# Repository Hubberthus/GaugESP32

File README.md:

# GaugESP32
A merge of the [SparkFun ESP32 Thing](https://www.sparkfun.com/products/13907) and [SparkFun Battery Babysitter](https://www.sparkfun.com/products/13777) boards

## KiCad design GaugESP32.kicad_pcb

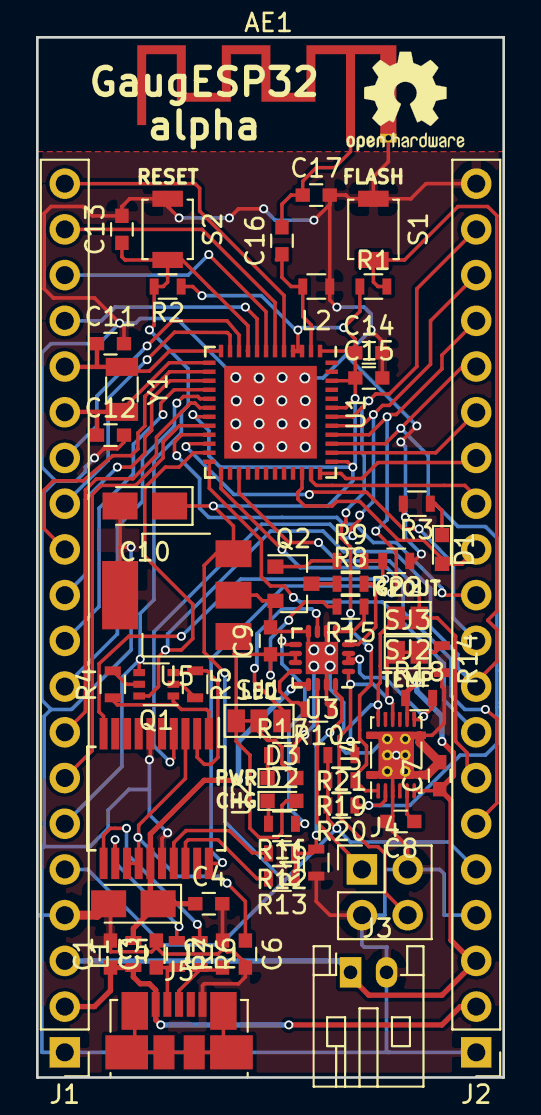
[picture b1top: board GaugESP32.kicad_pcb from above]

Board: 2 copper layers, 25.9 x 57.8 mm, 63 parts (0 on the bottom side), 64 nets.

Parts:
AE1: Antenna_Shield; Texas_SWRA117D_2.4GHz_Left
C1, C4, C6, C13, C15: 0.1uF; C_0603
C2, C3: 47pF; C_0603
C5, C10: 4.7F; CP_Tantalum_Case-A_EIA-3216-18_Reflow
C7, C9: 1uF; C_0603
C8: 0.47uF; C_0603
C11, C12: 15pF; C_0603
C14: 10uF; C_0603
C16: 4.7pF; C_0603
C17: 2.7pF; C_0603
D1: BLUE; LED_0603
D2: YELLOW; LED_0603
D3: RED; LED_0603
J1, J2: Conn_01x20; Pin_Header_Straight_1x20_Pitch2.54mm
J3: JST-PH; JST_PH_S2B-PH-K_02x2.00mm_Angled
J4: Conn_02x02_Counter_Clockwise; Pin_Header_Straight_2x02_Pitch2.54mm
J5: Micro USB-B; USB_Micro-B_Molex_47346-0001
L1: 600R/2A; L_0603
L2: 1.6nH; L_0603
Q1: MBT3946DW1T1; SOT-363_SC-70-6
Q2: BC847; SOT-23
R1, R2, R4, R5, R14, R15: 10k; R_0603
R3: 330; R_0603
R6, R7: 27; R_0603
R8: 100k; R_0603
R9: 470; R_0603
R10: 1.1k; R_0603
R11: 8.9k; R_0603
R12: 2.4k; R_0603
R13: 860; R_0603
R16: 180; R_0603
R17: 1k; R_0603
R18: 0.01; R_0603
R19, R20, R21: 4.7k; R_0603
R22: 2.2k; R_0603
S1: FLASH; SW_SPST_B3U-1000P
S2: RESET; SW_SPST_B3U-1000P
SJ1: GS3
SJ2, SJ3: GS2
U1: ESP32PICO_D4; ESP32_PICO_D4
U2: FT231XS; SSOP-20_5.3x7.2mm_Pitch0.65mm
U3: BQ24075; QFN-16-1EP_3x3mm_Pitch0.5mm
U4: BQ27441-G1; Texas_S-PDSO-N12
U5: LM3940; SOT-223
Y1: 32.768kHz; Crystal_SMD_3215-2pin_3.2x1.5mm

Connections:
+3.3VA: C10.1, C14.1, C15.1, J1.5, J2.5, R1.1, R2.1, R19.2, R20.2, R21.2, U1.1, U1.3, U1.4, U1.19, U1.37, U1.43, U1.46, U5.3
+5V: C4.1, C5.1, L1.2, U2.15, U3.13
+BATT: R18.2, U3.2, U3.3, U4.7
/1.8V: C8.1, U4.5
BCD#: R13.2, U2.18
DTR: Q1.1, R4.1, U2.1
EN: C13.1, J1.6, Q1.4, R2.2, S2.2, U1.9
GND: AE1.2, C1.2, C2.2, C3.2, C4.2, C5.2, C6.2, C7.2, C8.2, C9.2, C10.2, C11.2, C12.2, C13.2, C14.2, C15.2, C17.2, J1.1, J1.4, J2.1, J2.4, J2.20, J3.2, J4.2, J4.3, J5.5, L2.1, Q2.2, R3.2, R10.1, R11.1, R14.2, R17.2, R22.1, S1.1, S2.1, U1.49, U2.6, U2.16, U3.6, U3.8, U3.15, U3.17, U4.3, U4.13, U5.2, U5.4
GPOUT: J2.7, R21.1, SJ2.1, SJ2.2, U1.27, U4.12
IO0: J2.9, Q1.6, R1.2, S1.2, U1.23
IO2: J2.10, U1.22
IO4: J2.8, U1.24
IO5: D1.2, J2.12, U1.34
IO12: J1.8, U1.18
IO13: J1.7, U1.20
IO14: J1.9, U1.17
IO15: J2.11, U1.21
IO16: J2.6, U1.25
IO18: J2.13, U1.35
IO19: J2.15, U1.38
IO21: J2.19, R19.1, U1.42, U4.1
IO22: J2.16, R20.1, U1.39, U4.2
IO23: J2.14, U1.36
IO25: J1.12, U1.14
IO26: J1.11, U1.15
IO27: J1.10, U1.16
IO32: C11.1, J1.16, U1.12, Y1.2
IO33: C12.1, J1.15, U1.13, Y1.1
IO34: J1.14, U1.10
IO35: J1.13, U1.11
IO36: J1.20, U1.5
IO37: J1.19, U1.6
IO38: J1.18, U1.7
IO39: J1.17, U1.8
LNA: C16.1, L2.2, U1.2
unnamed: AE1.1, C16.2, C17.1
unnamed: C2.1, J5.3, R6.2
unnamed: C3.1, J5.2, R7.2
unnamed: C6.1, U2.3, U2.13, U2.14
unnamed: D1.1, R3.1
unnamed: D2.1, R16.2
unnamed: D3.1, R17.1
unnamed: Q1.2, R5.2
unnamed: Q1.5, R4.2
unnamed: Q2.1, R9.1
unnamed: Q2.3, R8.1
unnamed: R6.1, U2.11
unnamed: R7.1, U2.12
unnamed: R8.2, U3.4
unnamed: R10.2, U3.12
unnamed: R11.2, R12.1, R13.1, U3.16
unnamed: R15.1, U3.5
unnamed: R16.1, U3.9
unnamed: SJ1.1, U3.7
PWREN#: R12.2, U2.17
RTS: Q1.3, R5.1, U2.2
RXD0: J2.17, U1.40, U2.20
SLEEP#: R9.2, R22.2, U2.10
TMR: J4.1, U3.14
TS: J4.4, R14.1, SJ3.1, SJ3.2, U3.1, U4.10
TXD0: J2.18, U1.41, U2.4
VBATT-RAW: C7.1, J1.3, J2.3, J3.1, R18.1, U4.6, U4.8
VSYS: C9.1, D2.2, D3.2, R15.2, SJ1.2, SJ1.3, U3.10, U3.11, U5.1
VUSB-RAW: C1.1, J1.2, J2.2, J5.1, L1.1

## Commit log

2018-04-24 Minor fixes
2018-06-06 V2 with ESP32-PICO-D4, and initial board
2018-06-08 Main ESP32 components placement
2018-06-21 Board layout placement
2018-07-16 Layout work
2018-07-17 Layout trace complete
2018-07-18 Layout tracing and fill finalization
